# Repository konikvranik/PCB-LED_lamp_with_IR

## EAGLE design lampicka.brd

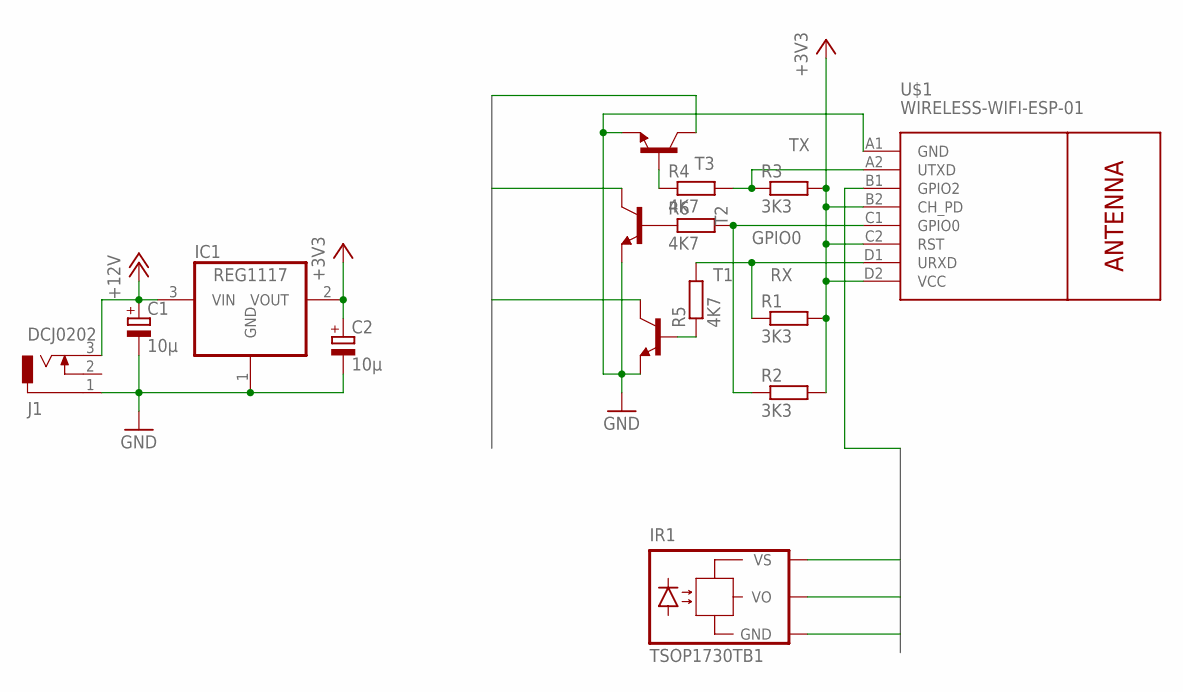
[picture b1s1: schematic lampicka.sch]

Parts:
C1, C2: 10µ; D/7343-31R
IC1: REG1117; SOT223
IR1: TSOP1730TB1; TSOP17_TB1
J1: DCJ0202
R1, R2, R3: 3K3; M1206
R4, R5, R6: 4K7; M1206
T1, T2, T3: MMBT2222ALT1-NPN-SOT23-BEC; SOT23-BEC
U$1: WIRELESS-WIFI-ESP-01

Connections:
+3V3: C2.+, IC1.2 (VOUT), IR1.VS, R1.2, R2.2, R3.2, U$1.B2 (CH_PD), U$1.C2 (RST), U$1.D2 (VCC)
+12V: C1.+, IC1.3 (VIN), J1.3
BLUE: T1.C
GND: C1.-, C2.-, IC1.1 (GND), IR1.GND, J1.1, T1.E, T2.E, T3.E, U$1.A1 (GND)
GPIO0: R2.1, R6.2, U$1.C1 (GPIO0)
GREEN: T3.C
IR: IR1.VO, U$1.B1 (GPIO2)
unnamed: R6.1, T3.B
unnamed: R5.1, T1.B
unnamed: R4.1, T2.B
RED: T2.C
RX: R1.1, R5.2, U$1.D1 (URXD)
TX: R3.1, R4.2, U$1.A2 (UTXD)

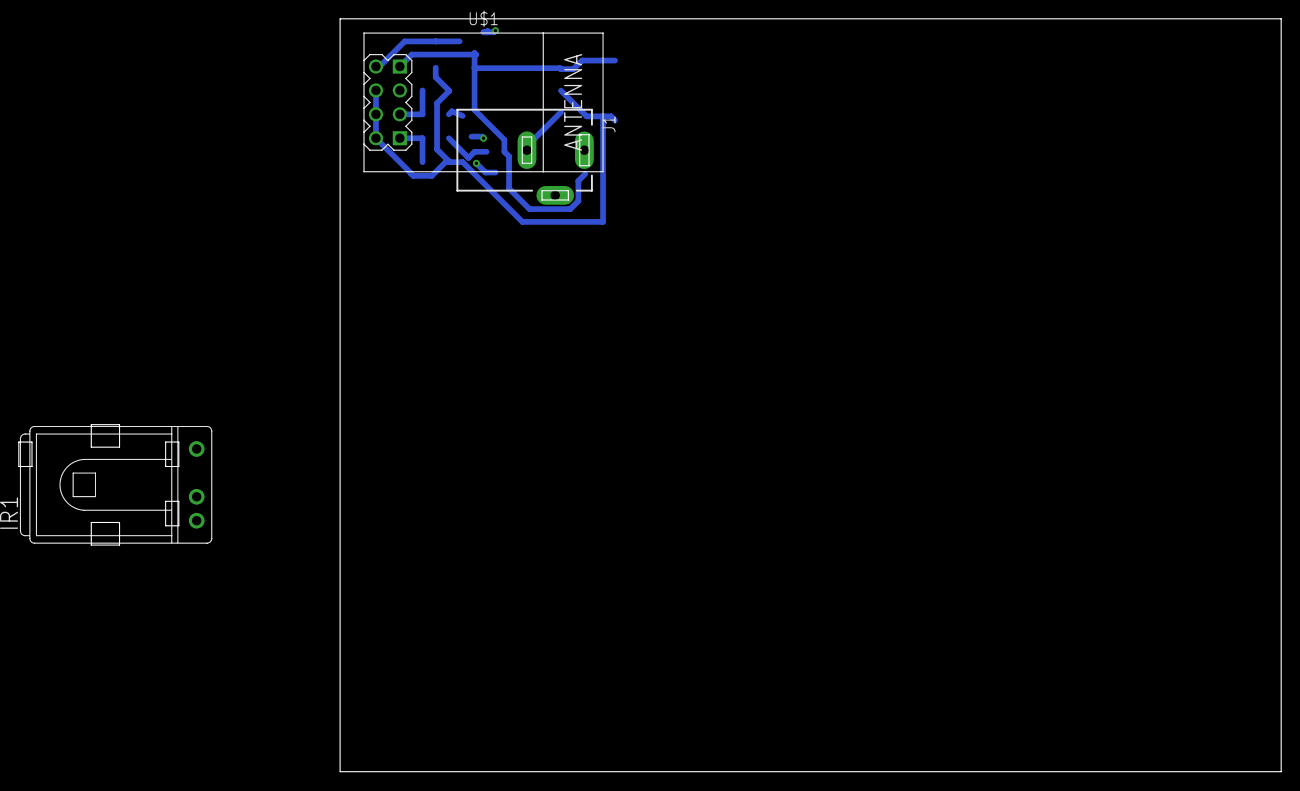
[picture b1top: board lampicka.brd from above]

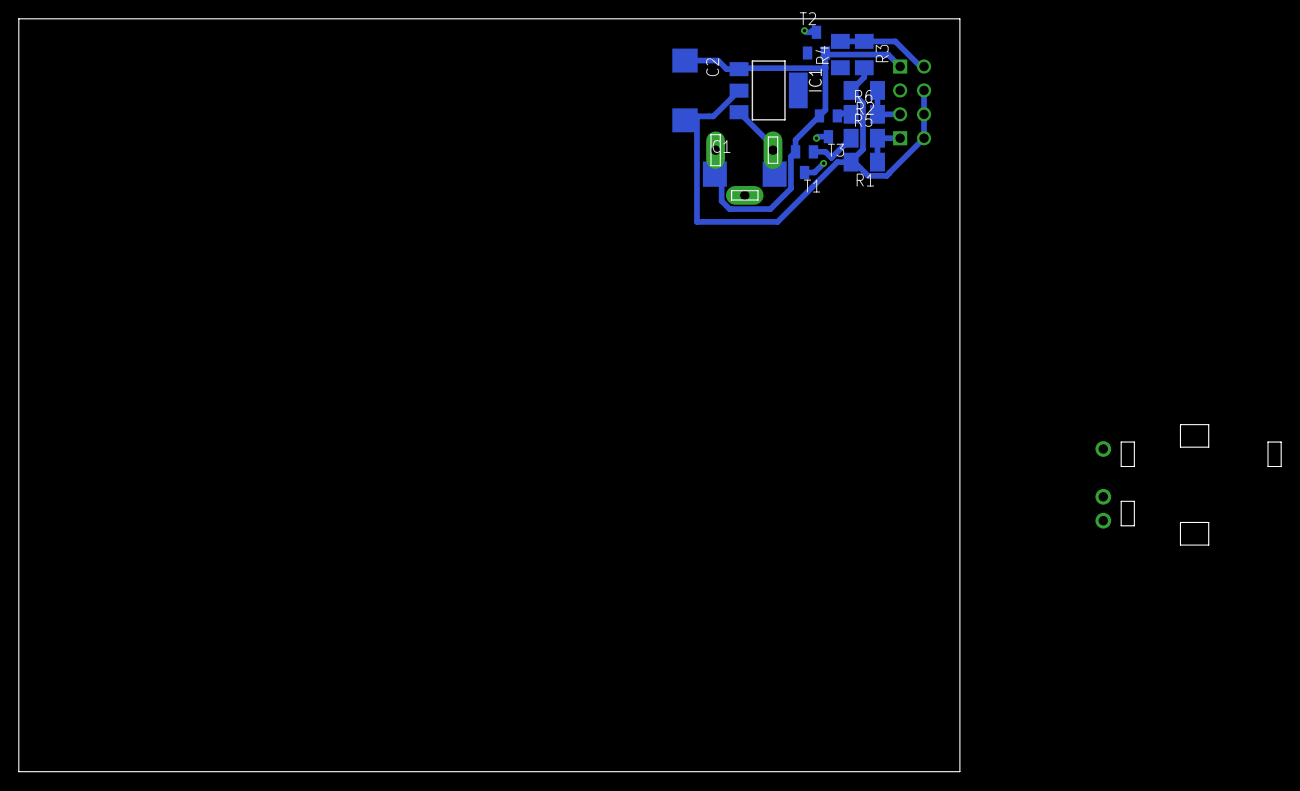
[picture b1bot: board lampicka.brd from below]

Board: 2 copper layers, 100.0 x 80.0 mm, 15 parts (12 on the bottom side), 10 nets.

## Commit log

2019-10-21 lampicka
2019-10-21 lampickaIR
2019-10-29 pcb transistors
2019-10-29 IR + SOT transistors
2019-11-04 no 10k resistors
2019-11-06 no 10k resistors routed
2019-11-17 addressable
2020-02-13 kikcad
2020-02-13 lamp
2020-02-14 leds
2020-02-15 settings
2020-02-15 pins

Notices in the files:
parts and their libraries:
diy-modules: Released under the Creative Commons Attribution 4.0 International License: http://creativecommons.org/licenses/by/4.0
